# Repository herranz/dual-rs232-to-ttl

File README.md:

# Dual RS232 to TTL converter
> Simple dual channel RS232 to TTL converter using the MAX3232.

## Table of Contents
* [General Info](#general-information)
* [Features](#features)
* [Screenshots](#screenshots)
* [Setup](#setup)
* [Usage](#usage)
* [Project Status](#project-status)
* [Room for Improvement](#room-for-improvement)
* [Acknowledgements](#acknowledgements)
* [Contact](#contact)
* [License](#license)

## General Information
- This is a simple breakout board for a MAX3232 that allow you to convert old devices with RS232 into a microcontroller UART
<!-- You don't have to answer all the questions - just the ones relevant to your project. -->

## Features
- Is a simple converter, what else do you want!?

## Screenshots

<!-- If you have screenshots you'd like to share, include them here. -->

## Setup
None

## Usage
None

## Project Status
Project is:  _complete_ 

## Room for Improvement
Maybe develop an alternative PCB with dual DB9 connectors?

## Acknowledgements
- none

## Contact
Created by [@herranz]- feel free to contact me!

 ## License 
 This project is open source and available under the [CERN-OHL-W](https://ohwr.org/cern_ohl_w_v2.txt).

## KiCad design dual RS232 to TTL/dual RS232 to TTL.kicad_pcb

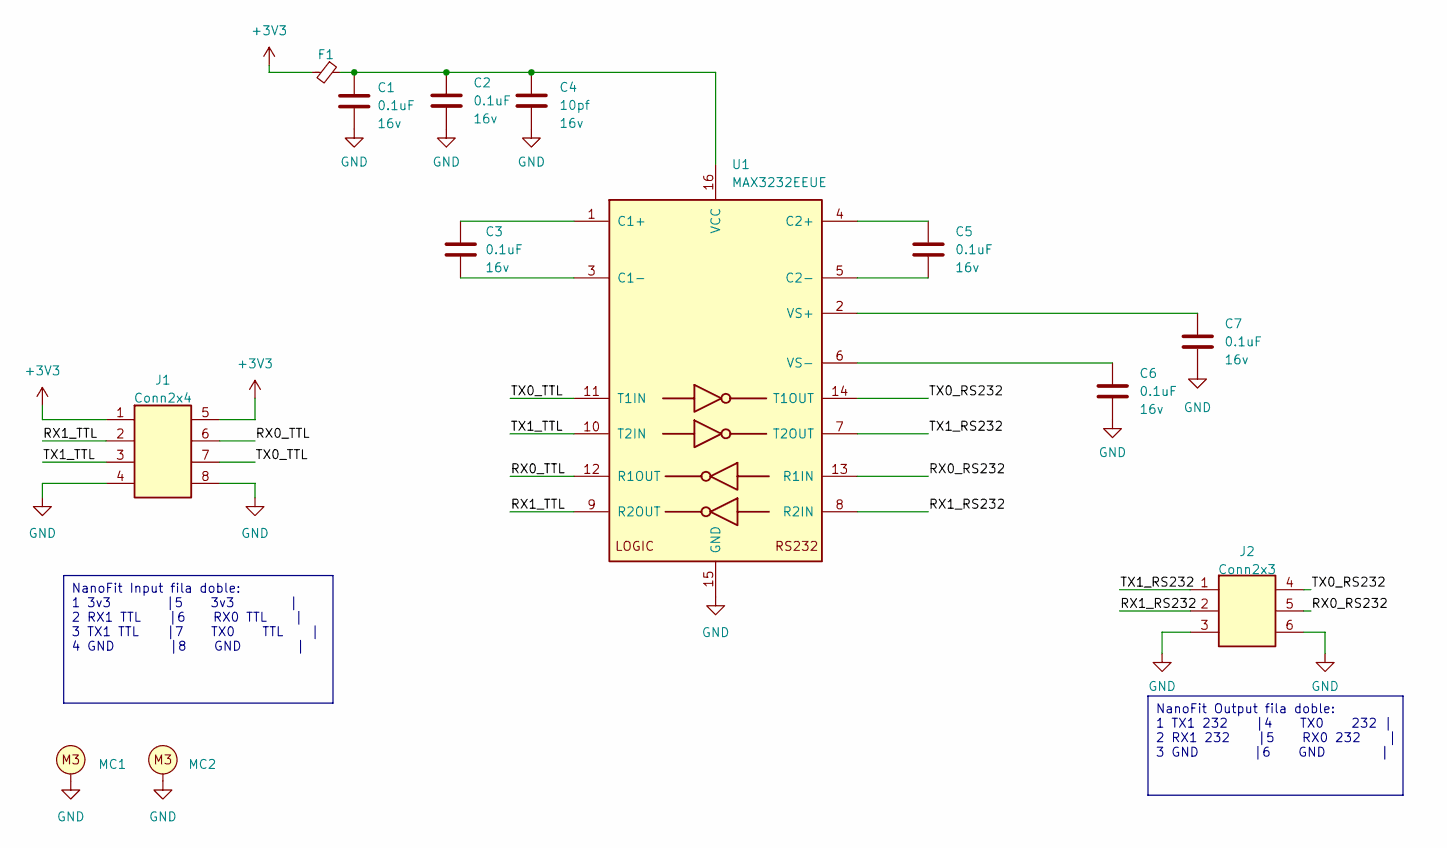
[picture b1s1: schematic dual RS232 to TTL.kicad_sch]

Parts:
C1: 0.1uF; C_0805_2012Metric; Voltage 16v
C2, C3, C5, C6, C7: 0.1uF; C_0402_1005Metric; Voltage 16v
C4: 10pf; C_0402_1005Metric; Voltage 16v
F1: L_0402_1005Metric_Pad0.77x0.64mm_HandSolder
J1: Conn2x4; Molex_Nano-Fit_105314-xx08_2x04_P2.50mm_Horizontal
J2: Conn2x3; Molex_Nano-Fit_105314-xx06_2x03_P2.50mm_Horizontal; MPN 1053141106
MC1, MC2: M3_Hole
U1: MAX3232EEUE; SOP65P640X110-16N

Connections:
+3V3: F1.1, J1.1, J1.5
/RX0_RS232: J2.5, U1.13 (R1IN)
/RX0_TTL: J1.6, U1.12 (R1OUT)
/RX1_RS232: J2.2, U1.8 (R2IN)
/RX1_TTL: J1.2, U1.9 (R2OUT)
/TX0_RS232: J2.4, U1.14 (T1OUT)
/TX0_TTL: J1.7, U1.11 (T1IN)
/TX1_RS232: J2.1, U1.7 (T2OUT)
/TX1_TTL: J1.3, U1.10 (T2IN)
GND: C1.2, C2.2, C4.2, C6.2, C7.2, J1.4, J1.8, J2.3, J2.6, MC1.1, MC2.1, U1.15 (GND)
unnamed: C3.1, U1.1 (C1+)
unnamed: C3.2, U1.3 (C1-)
unnamed: C5.1, U1.4 (C2+)
unnamed: C5.2, U1.5 (C2-)
unnamed: C1.1, C2.1, C4.1, F1.2, U1.16 (VCC)
unnamed: C7.1, U1.2 (VS+)
unnamed: C6.1, U1.6 (VS-)

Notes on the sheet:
NanoFit Output fila doble: 1 TX1 232 |4 TX0 232 | 2 RX1 232 |5 RX0 232 | 3 GND |6 GND |
NanoFit Input fila doble: 1 3v3 |5 3v3 | 2 RX1 TTL |6 RX0 TTL | 3 TX1 TTL |7 TX0 TTL | 4 GND |8 GND |

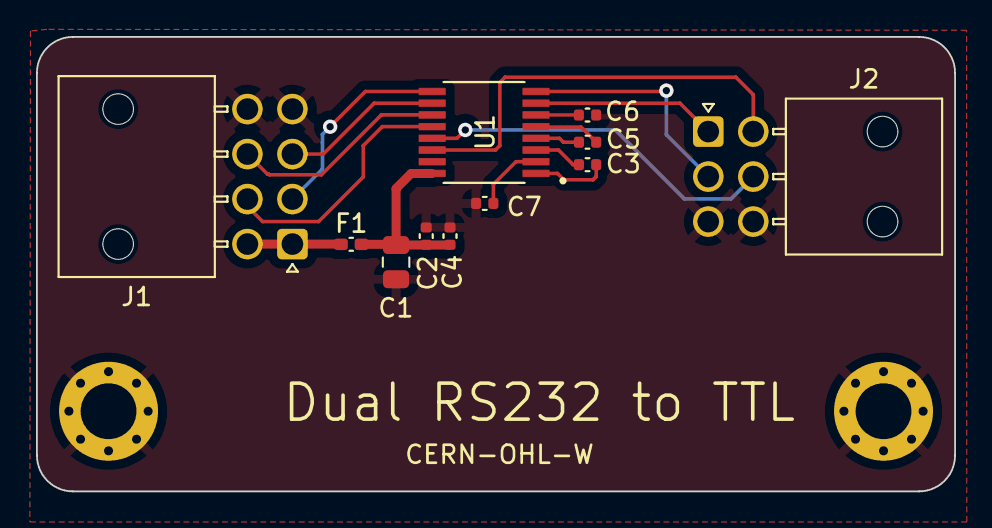
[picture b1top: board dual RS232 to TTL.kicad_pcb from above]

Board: 2 copper layers, 51.0 x 25.2 mm, 13 parts (0 on the bottom side), 17 nets.

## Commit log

2023-11-02 inicio proyecto
2023-11-03 finalizado el esquema
2023-11-03 finalizado PCB
2023-11-03 update casi finalizado
2023-11-04 PCB acabada
2023-11-04 añadido de la licencia en la PCB
2023-11-06 Añadido agujero al PCB y Creado el archivo de producción
